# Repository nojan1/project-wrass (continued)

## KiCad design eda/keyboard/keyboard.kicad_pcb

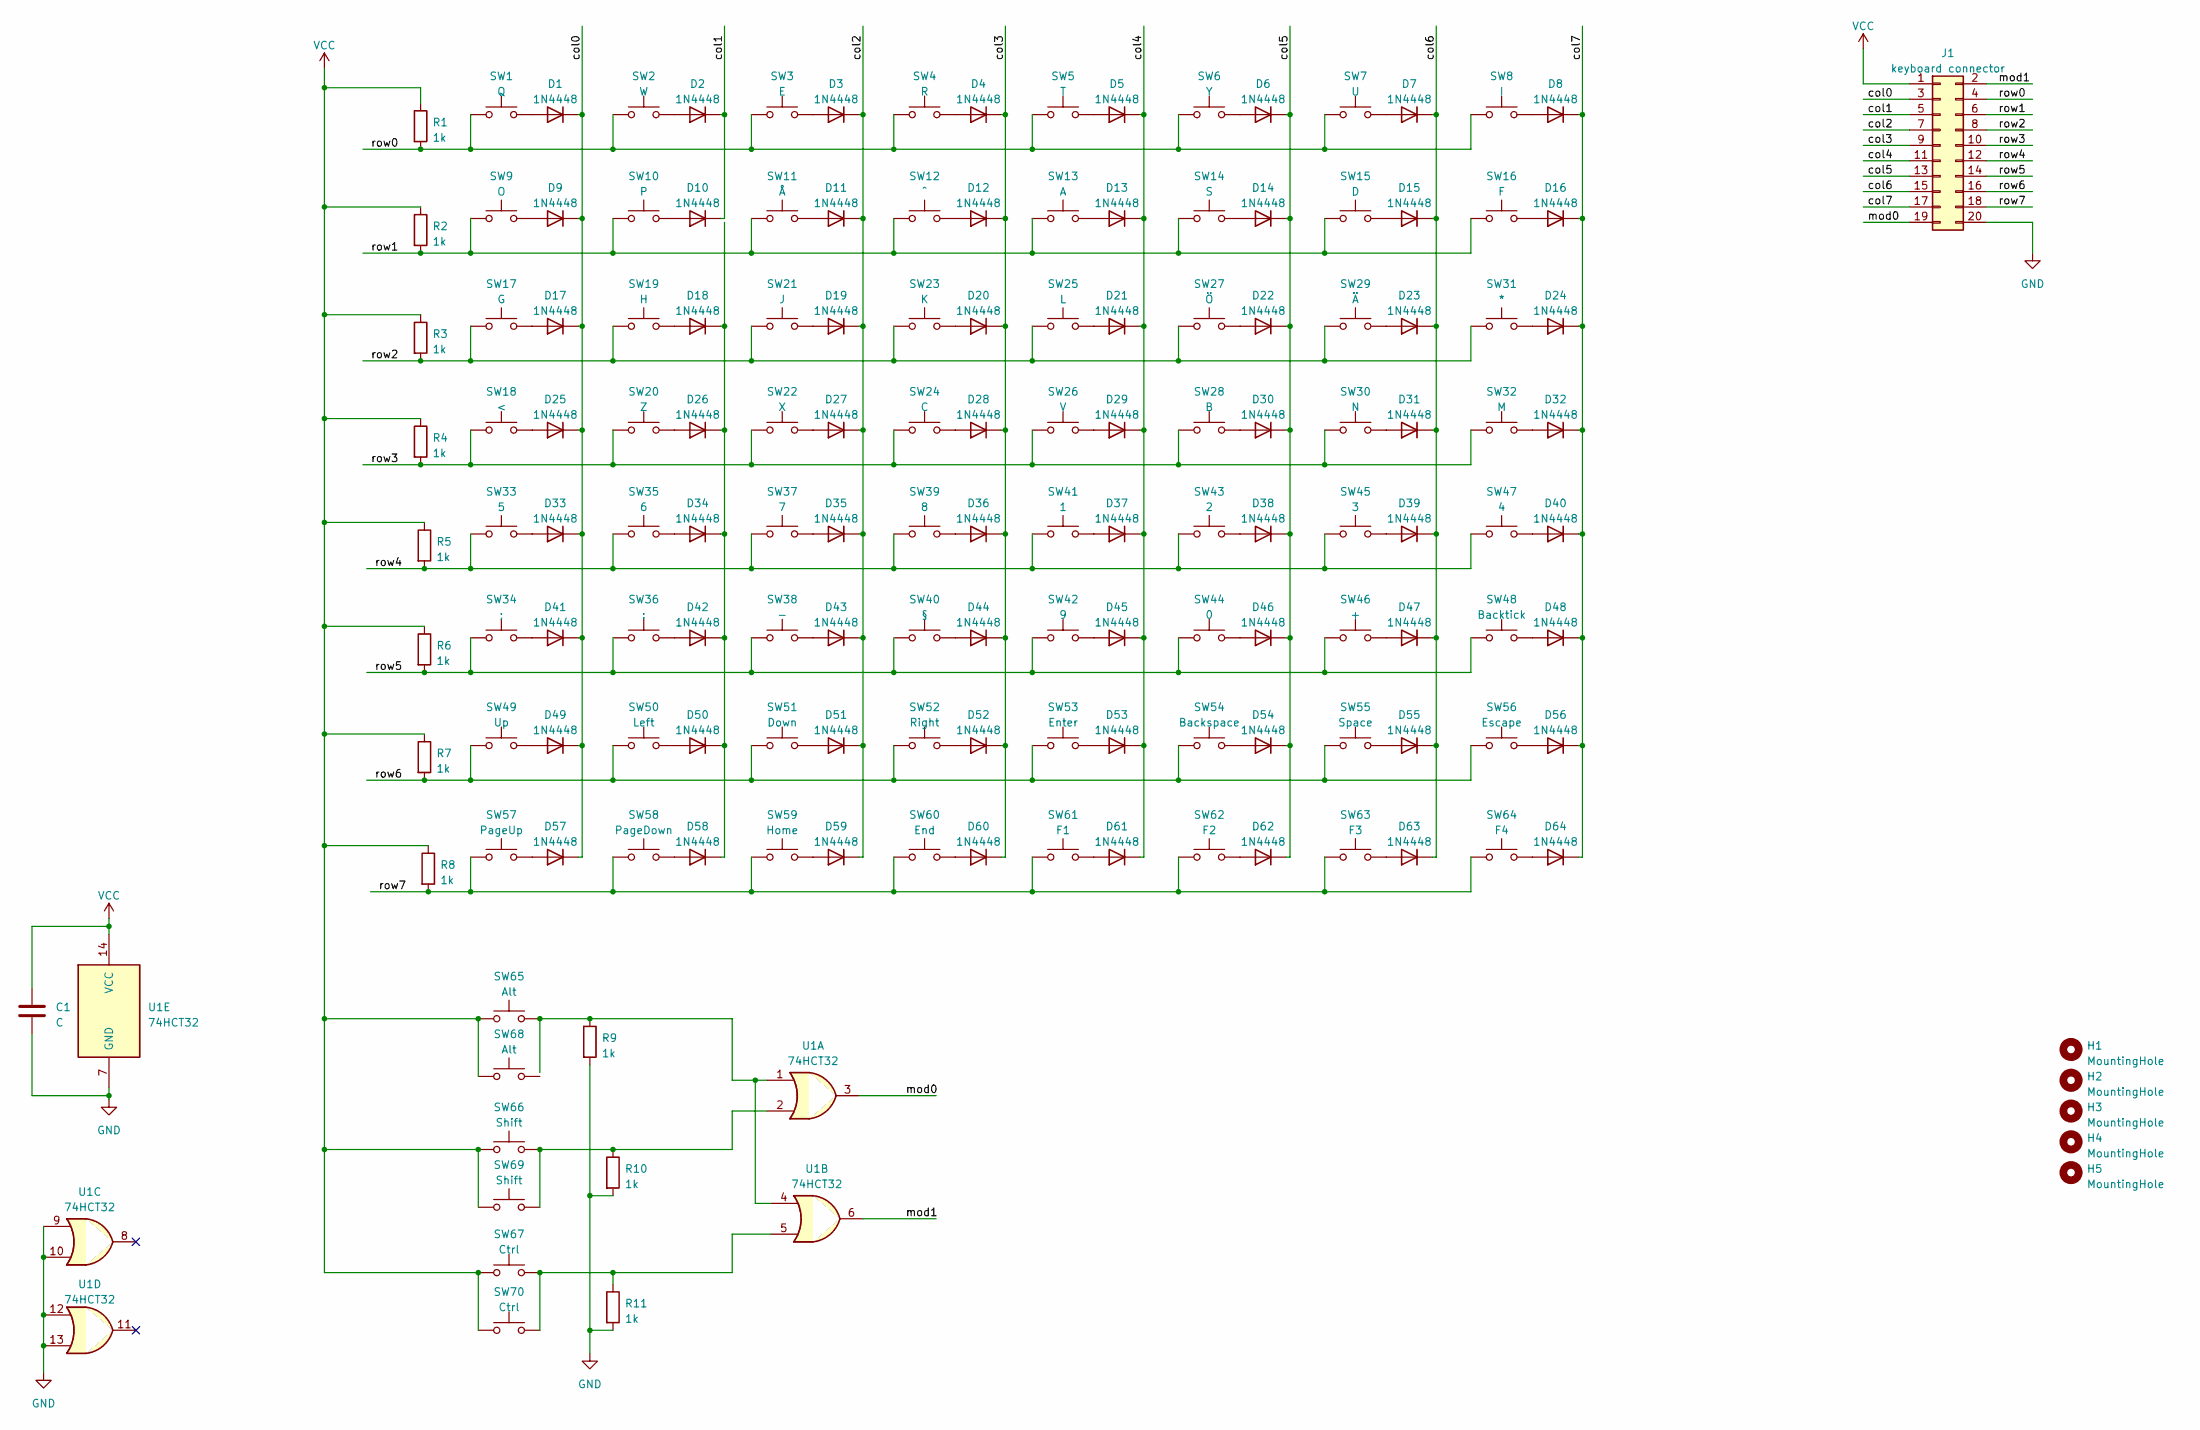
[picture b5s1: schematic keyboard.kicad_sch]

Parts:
C1: C
D1, D2, D3, D4, D5, D6, D7, D8, D9, D10, D11, D12, D13, D14, D15, D16, D17, D18, D19, D20, D21, D22, D23, D24, D25, D26, D27, D28, D29, D30, D31, D32, D33, D34, D35, D36, D37, D38, D39, D40, D41, D42, D43, D44, D45, D46, D47, D48, D49, D50, D51, D52, D53, D54, D55, D56, D57, D58, D59, D60, D61, D62, D63, D64: 1N4448; D_DO-35_SOD27_P7.62mm_Horizontal
H1, H2, H3, H4, H5: MountingHole; MountingHole_2.5mm
J1: keyboard connector; PinSocket_2x10_P2.54mm_Horizontal
R1, R2, R3, R4, R5, R6, R7, R8, R9, R10, R11: 1k
SW1: Q; SW_Cherry_MX_PCB_1.00u
SW2: W; SW_Cherry_MX_PCB_1.00u
SW3: E; SW_Cherry_MX_PCB_1.00u
SW4: R; SW_Cherry_MX_PCB_1.00u
SW5: T; SW_Cherry_MX_PCB_1.00u
SW6: Y; SW_Cherry_MX_PCB_1.00u
SW7: U; SW_Cherry_MX_PCB_1.00u
SW8: I; SW_Cherry_MX_PCB_1.00u
SW9: O; SW_Cherry_MX_PCB_1.00u
SW10: P; SW_Cherry_MX_PCB_1.00u
SW11: Å; SW_Cherry_MX_PCB_1.00u
SW12: ^; SW_Cherry_MX_PCB_1.00u
SW13: A; SW_Cherry_MX_PCB_1.00u
SW14: S; SW_Cherry_MX_PCB_1.00u
SW15: D; SW_Cherry_MX_PCB_1.00u
SW16: F; SW_Cherry_MX_PCB_1.00u
SW17: G; SW_Cherry_MX_PCB_1.00u
SW18: <; SW_Cherry_MX_PCB_1.00u
SW19: H; SW_Cherry_MX_PCB_1.00u
SW20: Z; SW_Cherry_MX_PCB_1.00u
SW21: J; SW_Cherry_MX_PCB_1.00u
SW22: X; SW_Cherry_MX_PCB_1.00u
SW23: K; SW_Cherry_MX_PCB_1.00u
SW24: C; SW_Cherry_MX_PCB_1.00u
SW25: L; SW_Cherry_MX_PCB_1.00u
SW26: V; SW_Cherry_MX_PCB_1.00u
SW27: Ö; SW_Cherry_MX_PCB_1.00u
SW28: B; SW_Cherry_MX_PCB_1.00u
SW29: Ä; SW_Cherry_MX_PCB_1.00u
SW30: N; SW_Cherry_MX_PCB_1.00u
SW31: *; SW_Cherry_MX_PCB_1.00u
SW32: M; SW_Cherry_MX_PCB_1.00u
SW33: 5; SW_Cherry_MX_PCB_1.00u
SW34: ;; SW_Cherry_MX_PCB_1.00u
SW35: 6; SW_Cherry_MX_PCB_1.00u
SW36: :; SW_Cherry_MX_PCB_1.00u
SW37: 7; SW_Cherry_MX_PCB_1.00u
SW38: -; SW_Cherry_MX_PCB_1.00u
SW39: 8; SW_Cherry_MX_PCB_1.00u
SW40: §; SW_Cherry_MX_PCB_1.00u
SW41: 1; SW_Cherry_MX_PCB_1.00u
SW42: 9; SW_Cherry_MX_PCB_1.00u
SW43: 2; SW_Cherry_MX_PCB_1.00u
SW44: 0; SW_Cherry_MX_PCB_1.00u
SW45: 3; SW_Cherry_MX_PCB_1.00u
SW46: +; SW_Cherry_MX_PCB_1.00u
SW47: 4; SW_Cherry_MX_PCB_1.00u
SW48: Backtick; SW_Cherry_MX_PCB_1.00u
SW49: Up; SW_Cherry_MX_PCB_1.00u
SW50: Left; SW_Cherry_MX_PCB_1.00u
SW51: Down; SW_Cherry_MX_PCB_1.00u
SW52: Right; SW_Cherry_MX_PCB_1.00u
SW53: Enter; SW_Cherry_MX_PCB_ISOEnter
SW54: Backspace; SW_Cherry_MX_PCB_2.00u
SW55: Space; SW_Cherry_MX_PCB_1.00u
SW56: Escape; SW_Cherry_MX_PCB_1.00u
SW57: PageUp; SW_Cherry_MX_PCB_1.00u
SW58: PageDown; SW_Cherry_MX_PCB_1.00u
SW59: Home; SW_Cherry_MX_PCB_1.00u
SW60: End; SW_Cherry_MX_PCB_1.00u
SW61: F1; SW_Cherry_MX_PCB_1.00u
SW62: F2; SW_Cherry_MX_PCB_1.00u
SW63: F3; SW_Cherry_MX_PCB_1.00u
SW64: F4; SW_Cherry_MX_PCB_1.00u
SW65, SW68: Alt; SW_Cherry_MX_PCB_1.25u
SW66: Shift; SW_Cherry_MX_PCB_1.25u
SW67, SW70: Ctrl; SW_Cherry_MX_PCB_1.25u
SW69: Shift; SW_Cherry_MX_PCB_2.75u
U1: 74HCT32; DIP-14_W10.16mm

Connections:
/col0: D1.1 (K), D9.1 (K), D17.1 (K), D25.1 (K), D33.1 (K), D41.1 (K), D49.1 (K), D57.1 (K), J1.3
/col1: D2.1 (K), D10.1 (K), J1.5
/col2: D3.1 (K), D11.1 (K), D19.1 (K), D27.1 (K), D35.1 (K), D43.1 (K), D51.1 (K), D59.1 (K), J1.7
/col3: D4.1 (K), D12.1 (K), D20.1 (K), D28.1 (K), D36.1 (K), D44.1 (K), D52.1 (K), D60.1 (K), J1.9
/col4: D5.1 (K), D13.1 (K), D21.1 (K), D29.1 (K), D37.1 (K), D45.1 (K), D53.1 (K), D61.1 (K), J1.11
/col5: D6.1 (K), D14.1 (K), D22.1 (K), D30.1 (K), D38.1 (K), D46.1 (K), D54.1 (K), D62.1 (K), J1.13
/col6: D7.1 (K), D15.1 (K), D23.1 (K), D31.1 (K), D39.1 (K), D47.1 (K), D55.1 (K), D63.1 (K), J1.15
/col7: D8.1 (K), D16.1 (K), D24.1 (K), D32.1 (K), D40.1 (K), D48.1 (K), D56.1 (K), D64.1 (K), J1.17
/mod0: J1.19, U1.3
/mod1: J1.2, U1.6
/row0: J1.4, R1.2, SW1.1, SW2.1, SW3.1, SW4.1, SW5.1, SW6.1, SW7.1, SW8.1
/row1: J1.6, R2.2, SW9.1, SW10.1, SW11.1, SW12.1, SW13.1, SW14.1, SW15.1, SW16.1
/row2: J1.8, R3.2, SW17.1, SW19.1, SW21.1, SW23.1, SW25.1, SW27.1, SW29.1, SW31.1
/row3: J1.10, R4.2, SW18.1, SW20.1, SW22.1, SW24.1, SW26.1, SW28.1, SW30.1, SW32.1
/row4: J1.12, R5.2, SW33.1, SW35.1, SW37.1, SW39.1, SW41.1, SW43.1, SW45.1, SW47.1
/row5: J1.14, R6.2, SW34.1, SW36.1, SW38.1, SW40.1, SW42.1, SW44.1, SW46.1, SW48.1
/row6: J1.16, R7.2, SW49.1, SW50.1, SW51.1, SW52.1, SW53.1, SW54.1, SW55.1, SW56.1
/row7: J1.18, R8.2, SW57.1, SW58.1, SW59.1, SW60.1, SW61.1, SW62.1, SW63.1, SW64.1
GND: C1.2, J1.20, R9.2, R10.2, R11.2, U1.7 (GND), U1.9, U1.10, U1.12, U1.13
unnamed: D1.2 (A), SW1.2
unnamed: D2.2 (A), SW2.2
unnamed: D3.2 (A), SW3.2
unnamed: D4.2 (A), SW4.2
unnamed: D5.2 (A), SW5.2
unnamed: D6.2 (A), SW6.2
unnamed: D7.2 (A), SW7.2
unnamed: D8.2 (A), SW8.2
unnamed: D9.2 (A), SW9.2
unnamed: D10.2 (A), SW10.2
unnamed: D11.2 (A), SW11.2
unnamed: D12.2 (A), SW12.2
unnamed: D13.2 (A), SW13.2
unnamed: D14.2 (A), SW14.2
unnamed: D15.2 (A), SW15.2
unnamed: D16.2 (A), SW16.2
unnamed: D17.2 (A), SW17.2
unnamed: D18.2 (A), SW19.2
unnamed: D18.1 (K), D26.1 (K), D34.1 (K), D42.1 (K), D50.1 (K), D58.1 (K)
unnamed: D19.2 (A), SW21.2
unnamed: D20.2 (A), SW23.2
unnamed: D21.2 (A), SW25.2
unnamed: D22.2 (A), SW27.2
unnamed: D23.2 (A), SW29.2
unnamed: D24.2 (A), SW31.2
unnamed: D25.2 (A), SW18.2
unnamed: D26.2 (A), SW20.2
unnamed: D27.2 (A), SW22.2
unnamed: D28.2 (A), SW24.2
unnamed: D29.2 (A), SW26.2
unnamed: D30.2 (A), SW28.2
unnamed: D31.2 (A), SW30.2
unnamed: D32.2 (A), SW32.2
unnamed: D33.2 (A), SW33.2
unnamed: D34.2 (A), SW35.2
unnamed: D35.2 (A), SW37.2
unnamed: D36.2 (A), SW39.2
unnamed: D37.2 (A), SW41.2
unnamed: D38.2 (A), SW43.2
unnamed: D39.2 (A), SW45.2
unnamed: D40.2 (A), SW47.2
unnamed: D41.2 (A), SW34.2
unnamed: D42.2 (A), SW36.2
unnamed: D43.2 (A), SW38.2
unnamed: D44.2 (A), SW40.2
unnamed: D45.2 (A), SW42.2
unnamed: D46.2 (A), SW44.2
unnamed: D47.2 (A), SW46.2
unnamed: D48.2 (A), SW48.2
unnamed: D49.2 (A), SW49.2
unnamed: D50.2 (A), SW50.2
unnamed: D51.2 (A), SW51.2
unnamed: D52.2 (A), SW52.2
unnamed: D53.2 (A), SW53.2
unnamed: D54.2 (A), SW54.2
unnamed: D55.2 (A), SW55.2
unnamed: D56.2 (A), SW56.2
unnamed: D57.2 (A), SW57.2
unnamed: D58.2 (A), SW58.2
unnamed: D59.2 (A), SW59.2
unnamed: D60.2 (A), SW60.2
unnamed: D61.2 (A), SW61.2
unnamed: D62.2 (A), SW62.2
unnamed: D63.2 (A), SW63.2
unnamed: D64.2 (A), SW64.2
unnamed: R9.1, SW65.2, U1.1, U1.4
unnamed: R10.1, SW66.2, SW69.2, U1.2
unnamed: R11.1, SW67.2, SW70.2, U1.5
VCC: C1.1, J1.1, R1.1, R2.1, R3.1, R4.1, R5.1, R6.1, R7.1, R8.1, SW65.1, SW66.1, SW67.1, SW68.1, SW69.1, SW70.1, U1.14 (VCC)

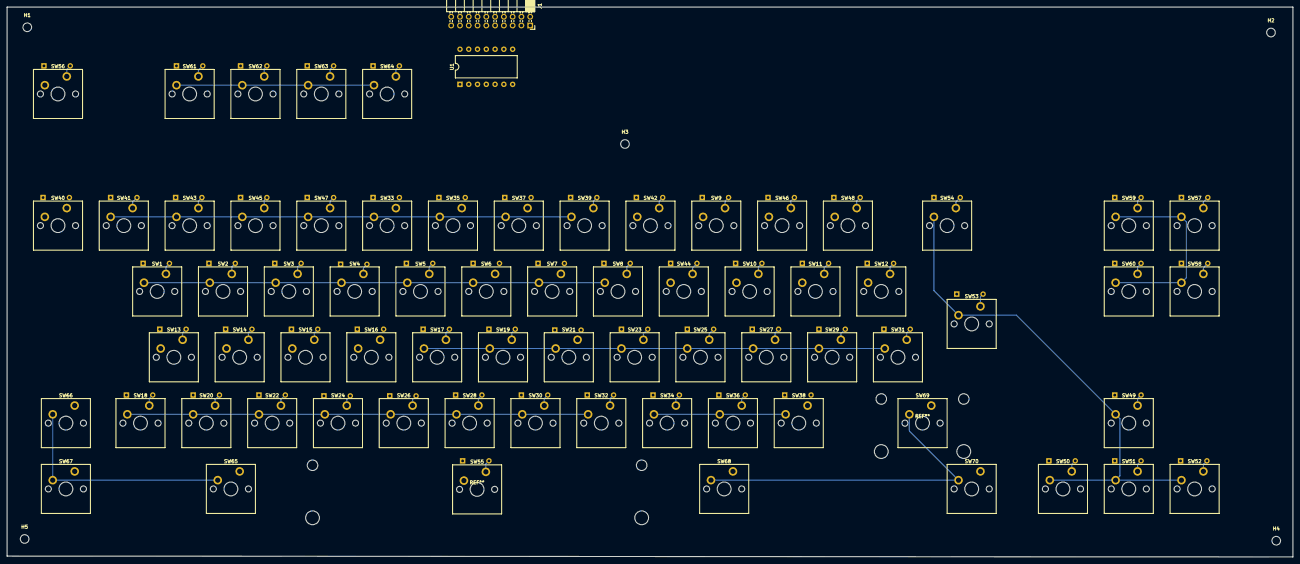
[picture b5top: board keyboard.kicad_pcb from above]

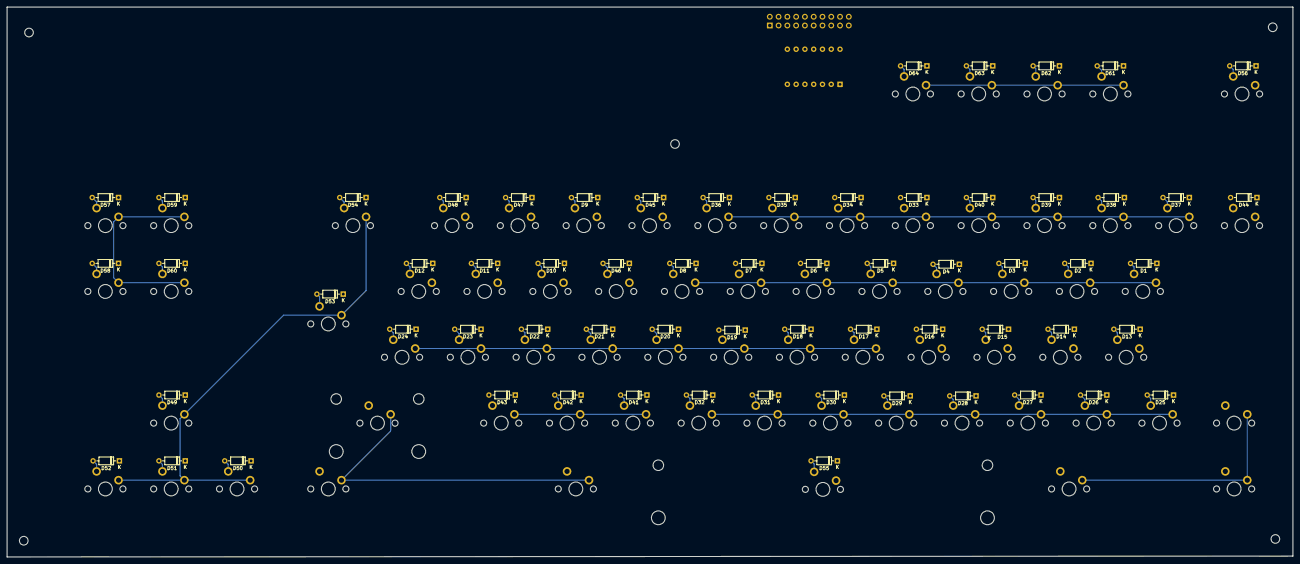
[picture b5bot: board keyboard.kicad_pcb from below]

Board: 2 copper layers, 372.1 x 159.1 mm, 141 parts (64 on the bottom side), 88 nets.

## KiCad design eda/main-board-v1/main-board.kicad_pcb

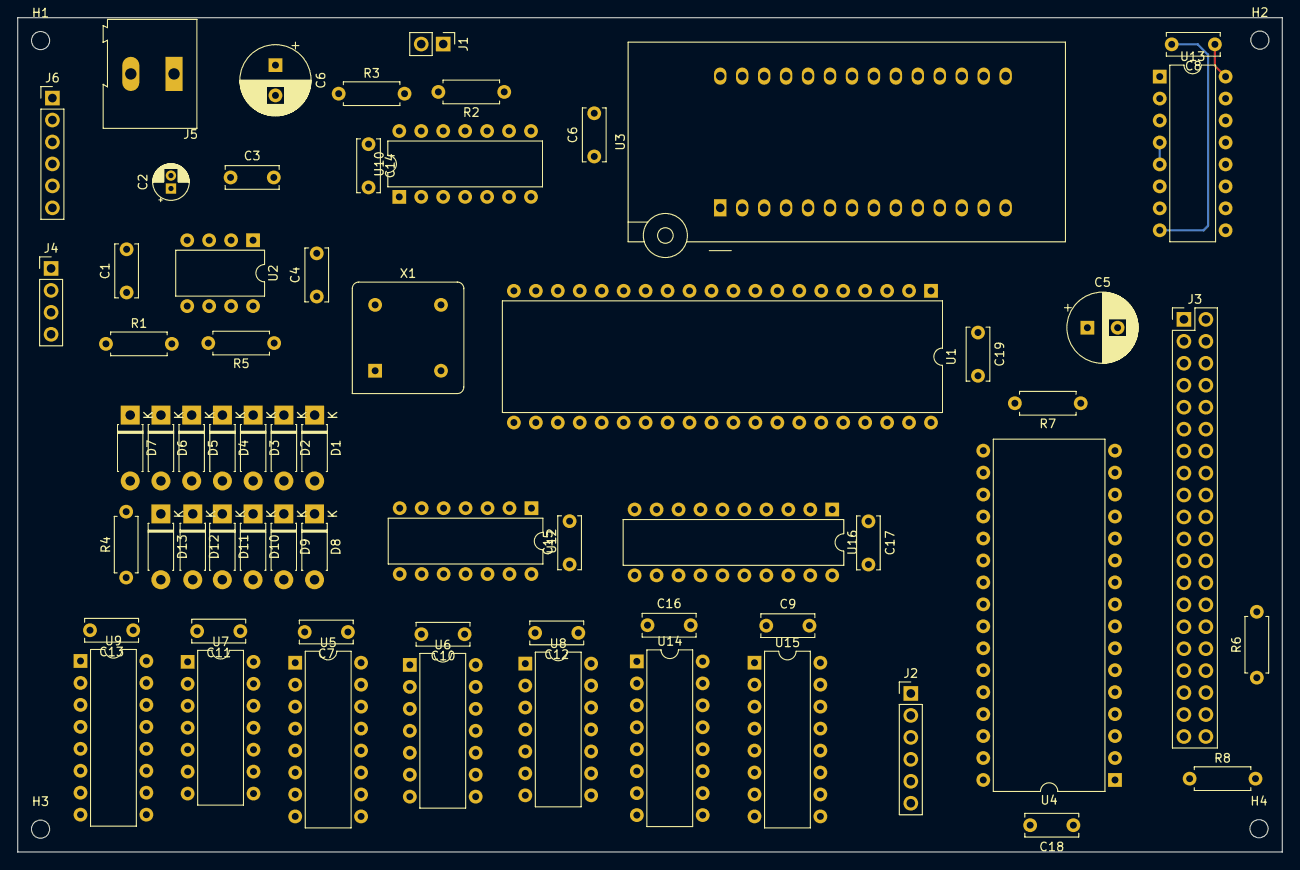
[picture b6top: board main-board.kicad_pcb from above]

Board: 2 copper layers, 146.3 x 96.5 mm, 67 parts (0 on the bottom side), 97 nets.

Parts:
C1: 10n; C_Disc_D6.0mm_W2.5mm_P5.00mm
C2: 10u; CP_Radial_D4.0mm_P1.50mm
C3, C4, C6, C7, C8, C9, C10, C11, C12, C13, C14, C15, C16, C17, C18, C19: 100n; C_Disc_D6.0mm_W2.5mm_P5.00mm
C5: 1u; CP_Radial_D8.0mm_P3.50mm
C6#2: 3u; CP_Radial_D8.0mm_P3.50mm
D1, D2, D3, D4, D5, D6, D7, D8, D9, D10, D11, D12, D13: 1N4007; D_DO-41_SOD81_P7.62mm_Horizontal
H1, H2, H3, H4: MountingHole; MountingHole_2.1mm
J1: RomHighSel; PinHeader_1x02_P2.54mm_Vertical
J2: Membank block; PinHeader_1x06_P2.54mm_Vertical
J3: Expansion; PinHeader_2x20_P2.54mm_Vertical
J4: $1-3 latch; PinHeader_1x04_P2.54mm_Vertical
J5: PWR; TerminalBlock_Altech_AK300-2_P5.00mm
J6: CS_leds; PinHeader_1x06_P2.54mm_Vertical
R1: 47k; R_Axial_DIN0207_L6.3mm_D2.5mm_P7.62mm_Horizontal
R2: 1M; R_Axial_DIN0207_L6.3mm_D2.5mm_P7.62mm_Horizontal
R3, R4, R6, R7, R8: 10k; R_Axial_DIN0207_L6.3mm_D2.5mm_P7.62mm_Horizontal
R5: 1k; R_Axial_DIN0207_L6.3mm_D2.5mm_P7.62mm_Horizontal
U1: W65C02SxP; DIP-40_W15.24mm
U2: NA555P; DIP-8_W7.62mm
U3: 28C256; DIP_Socket-28_W11.9_W12.7_W15.24_W17.78_W18.5_3M_228-1277-0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
U4: AS6C4008-55PCN; DIP-32_W15.24mm
U5, U13: 74HCT138; DIP-16_W7.62mm
U6, U12: 74HCT32; DIP-14_W7.62mm
U7: 74HCT08; DIP-14_W7.62mm
U8: 74HCT30; DIP-14_W7.62mm
U9: 74HCT139; DIP-16_W7.62mm
U10: 74HCT00; DIP-14_W7.62mm
U14, U15: 74LHCT157; DIP-16_W7.62mm
U16: 74HCT273; DIP-20_W7.62mm
X1: 4Mhz; Oscillator_DIP-8

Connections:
/A0: J3.3, U1.9 (A0)
/A1: J3.5, U1.10 (A1)
/A2: J3.7, U1.11 (A2)
/A3: J3.9, U1.12 (A3)
/A4: J3.11, U1.13 (A4)
/A5: J3.13, U1.14 (A5)
/A6: J3.15, U1.15 (A6)
/A7: J3.17, U1.16 (A7)
/A8: J3.19, U1.17 (A8)
/A9: J3.21, U1.18 (A9)
/A10: J3.23, U1.19 (A10)
/A11: J3.25, U1.20 (A11)
/A12: J3.27, U1.22 (A12)
/A13: J3.29, U1.23 (A13)
/A14: J3.31, U1.24 (A14)
/A15: J3.33, U1.25 (A15)
/Address decode/A0: U3.10 (A0), U4.12 (A0), U9.13 (A1)
/Address decode/A1: U3.9 (A1), U4.11 (A1), U9.14 (A0)
/Address decode/A2: D11.2 (A), U3.8 (A2), U4.10 (A2)
/Address decode/A3: D10.2 (A), U3.7 (A3), U4.9 (A3)
/Address decode/A4: D9.2 (A), U3.6 (A4), U4.8 (A4)
/Address decode/A5: D8.2 (A), U3.5 (A5), U4.7 (A5)
/Address decode/A6: D7.2 (A), U3.4 (A6), U4.6 (A6), U13.1 (A0)
/Address decode/A7: D6.2 (A), U3.3 (A7), U4.5 (A7), U13.2 (A1)
/Address decode/A8: D5.2 (A), U3.25 (A8), U4.27 (A8), U13.3 (A2)
/Address decode/A9: D4.2 (A), U3.24 (A9), U4.26 (A9), U9.3 (A1)
/Address decode/A10: D3.2 (A), U3.21 (A10), U4.23 (A10), U9.2 (A0)
/Address decode/A11: D2.2 (A), U3.23 (A11), U4.25 (A11), U10.1
/Address decode/A12: D1.2 (A), U3.2 (A12), U4.4 (A12), U10.2
/Address decode/A13: U3.26 (A13), U5.1 (A0), U14.3 (I1a)
/Address decode/A14: U5.2 (A1), U14.6 (I1b)
/Address decode/A15: U5.3 (A2), U14.10 (I1c)
/Address decode/Addr0Latch: U9.12 (O0), U16.11 (Cp)
/Address decode/Addr1Latch: J4.2, U9.11 (O1)
/Address decode/Addr2Latch: J4.3, U9.10 (O2)
/Address decode/Addr3Latch: J4.4, U9.9 (O3)
/Address decode/R~W: J3.37, U1.34 (R/~W), U4.29 (WE#), U10.9, U10.10
/Address decode/~Io1Cs: J6.5, U8.3, U9.5 (O1), U13.4 (E1), U13.5 (E2)
/Address decode/~Io2Cs: J6.6, U6.8, U8.4
/Address decode/~RamCs: J6.2, U4.22 (CE#), U12.3
/Address decode/~RamOe: U4.24 (OE#), U8.8, U12.1
/Address decode/~RomCs: U3.20 (~CS), U7.3
/Address decode/~RomOe: U3.22 (~OE), U10.8
/D0: J3.4, U1.33 (D0), U3.11 (D0), U4.13 (DQ0), U16.3 (D0)
/D1: J3.6, U1.32 (D1), U3.12 (D1), U4.14 (DQ1), U16.4 (D1)
/D2: J3.8, U1.31 (D2), U3.13 (D2), U4.15 (DQ2), U16.7 (D2)
/D3: J3.10, U1.30 (D3), U3.15 (D3), U4.17 (DQ3), U16.8 (D3)
/D4: J3.12, U1.29 (D4), U3.16 (D4), U4.18 (DQ4), U16.13 (D4)
/D5: J3.14, U1.28 (D5), U3.17 (D5), U4.19 (DQ5), U16.14 (D5)
/D6: J3.16, U1.27 (D6), U3.18 (D6), U4.20 (DQ6), U16.17 (D6)
/D7: J3.18, U1.26 (D7), U3.19 (D7), U4.21 (DQ7), U16.18 (D7)
/IO Address Decode/IoSelect0: J3.20, U13.15 (O0)
/IO Address Decode/IoSelect1: J3.22, U13.14 (O1)
/IO Address Decode/IoSelect2: J3.24, U13.13 (O2)
/IO Address Decode/IoSelect3: J3.26, U13.12 (O3)
/IO Address Decode/IoSelect4: J3.28, U13.11 (O4)
/IO Address Decode/IoSelect5: J3.30, U13.10 (O5)
/IO Address Decode/IoSelect6: J3.32, U13.9 (O6)
/IO Address Decode/IoSelect7: J3.34, U13.7 (O7)
/Memory banking/AB13: U4.28 (A13), U14.4 (Za)
/Memory banking/AB14: U4.3 (A14), U14.7 (Zb)
/Memory banking/AB15: U4.31 (A15), U14.9 (Zc)
/Memory banking/AB16: U4.2 (A16), U14.12 (Zd)
/Memory banking/AB17: U4.30 (A17), U15.4 (Za)
/Memory banking/AB18: U4.1 (A18), U15.7 (Zb)
/Memory banking/~Reset: J3.36, R5.2, U1.40 (~RES), U10.11, U16.1 (~Mr)
Clock: J3.35, U1.37 (ϕ0), X1.5 (OUT)
GND: C1.2, C2.2, C3.2, C4.2, C5.2, C6.2, C6#2.2, C7.2, C8.2, C9.2, C10.2, C11.2, C12.2, C13.2, C14.2, C15.2, C16.2, C17.2, C18.2, C19.2, J2.1, J3.2, J4.1, J5.2, R3.2, R4.2, U1.21 (VSS), U2.1 (GND), U3.14 (GND), U4.16 (VSS), U5.4 (E1), U5.5 (E2), U5.8 (GND), U6.7 (GND), U7.4, U7.5, U7.7 (GND), U7.9, U7.10, U7.12, U7.13, U8.7 (GND), U9.8 (GND), U10.4, U10.5, U10.7 (GND), U13.8 (GND), U14.8 (GND), U14.13 (I1d), U14.15 (E), U15.3 (I1a), U15.6 (I1b), U15.8 (GND), U15.10 (I1c), U15.11 (I0c), U15.13 (I1d), U15.14 (I0d), U15.15 (E), U16.10 (GND), X1.4 (GND)
unnamed: D1.1 (K), D2.1 (K), D3.1 (K), D4.1 (K), D5.1 (K), D6.1 (K), D7.1 (K), D8.1 (K), D9.1 (K), D10.1 (K), D11.1 (K), D12.1 (K), D13.1 (K), R4.1, U9.15 (E)
unnamed: J1.2, R3.1, U3.1 (A14)
unnamed: J2.2, U14.2 (I0a), U16.9 (Q3)
unnamed: J2.3, U14.5 (I0b), U16.12 (Q4)
unnamed: J2.4, U14.11 (I0c), U16.15 (Q5)
unnamed: J2.5, U15.2 (I0a), U16.16 (Q6)
unnamed: J2.6, U15.5 (I0b), U16.19 (Q7)
unnamed: J3.38, R7.2, U1.6 (~NMI)
unnamed: J3.39, R8.2, U1.2 (RDY), U1.36 (BE)
unnamed: J3.40, R6.2, U1.4 (~IRQ)
unnamed: J6.3, U6.3, U7.1, U8.1
unnamed: J6.4, U6.6, U7.2, U8.2
unnamed: C1.1, U2.5 (CV)
unnamed: C2.1, R1.2, U2.6 (THR), U2.7 (DIS)
unnamed: C3.1, R2.2, U2.2 (TR)
unnamed: U5.9 (O6), U6.1
unnamed: U5.7 (O7), U6.4
unnamed: U6.11, U9.1 (E)
unnamed: U6.9, U9.7 (O3)
unnamed: U6.12, U10.3
RamBank4Enable: U6.10, U16.2 (Q0)
RamBank5Enable: U6.2, U16.5 (Q1)
RamBank6Enable: U6.5, U16.6 (Q2)
Reset: U2.3 (Q), U10.12, U10.13
VCC: C4.1, C5.1, C6.1, C6#2.1, C7.1, C8.1, C9.1, C10.1, C11.1, C12.1, C13.1, C14.1, C15.1, C16.1, C17.1, C18.1, C19.1, J1.1, J3.1, J5.1, J6.1, R1.1, R2.1, R5.1, R6.1, R7.1, R8.1, U1.8 (VDD), U2.4 (R), U2.8 (VCC), U3.27 (~WE), U3.28 (VCC), U4.32 (VCC), U5.6 (E3), U5.16 (VCC), U6.14 (VCC), U7.14 (VCC), U8.5, U8.6, U8.11, U8.12, U8.14 (VCC), U9.16 (VCC), U10.14 (VCC), U13.6 (E3), U13.16 (VCC), U14.14 (I0d), U14.16 (VCC), U15.16 (VCC), U16.20 (VCC), X1.8 (Vcc)
~8000: U5.11 (O4), U14.1 (S), U15.1 (S)
~A000: U5.10 (O5), U6.13
~Clock: D13.2 (A), U1.3 (ϕ1), U12.2
~LowestBlock: D12.2 (A), U5.15 (O0)

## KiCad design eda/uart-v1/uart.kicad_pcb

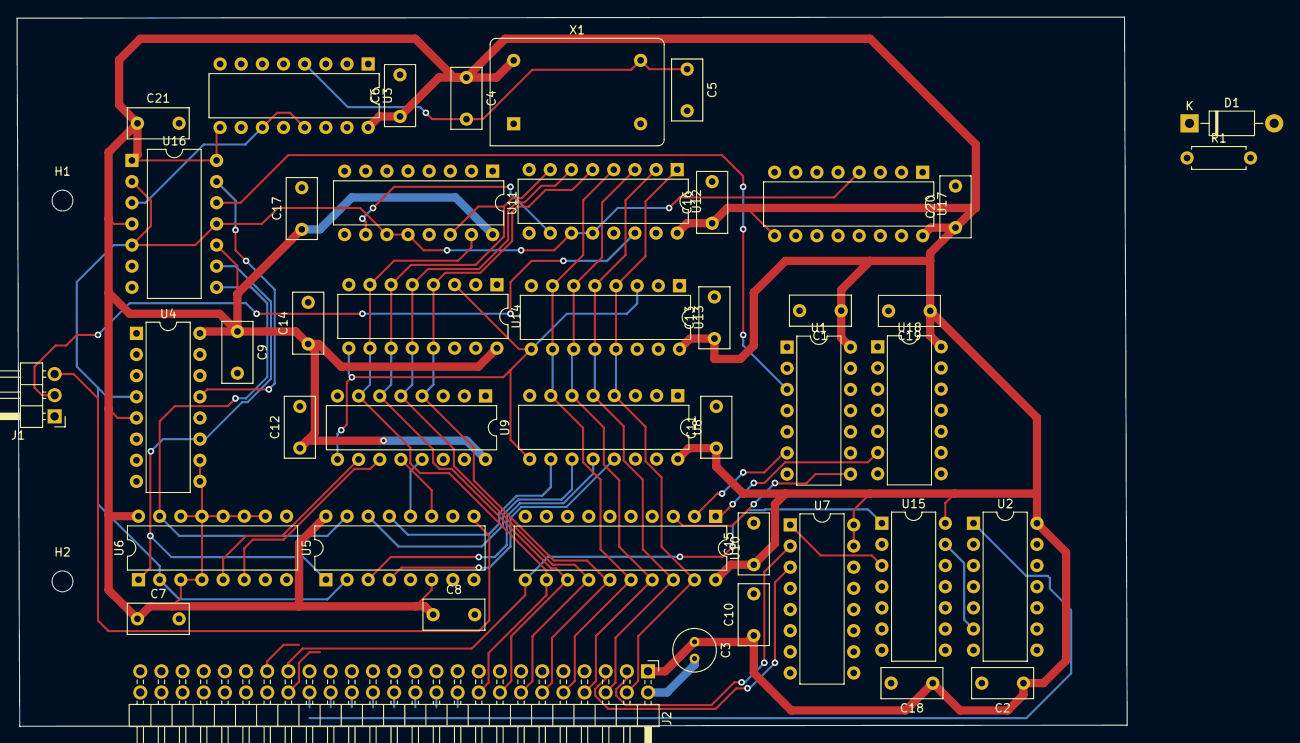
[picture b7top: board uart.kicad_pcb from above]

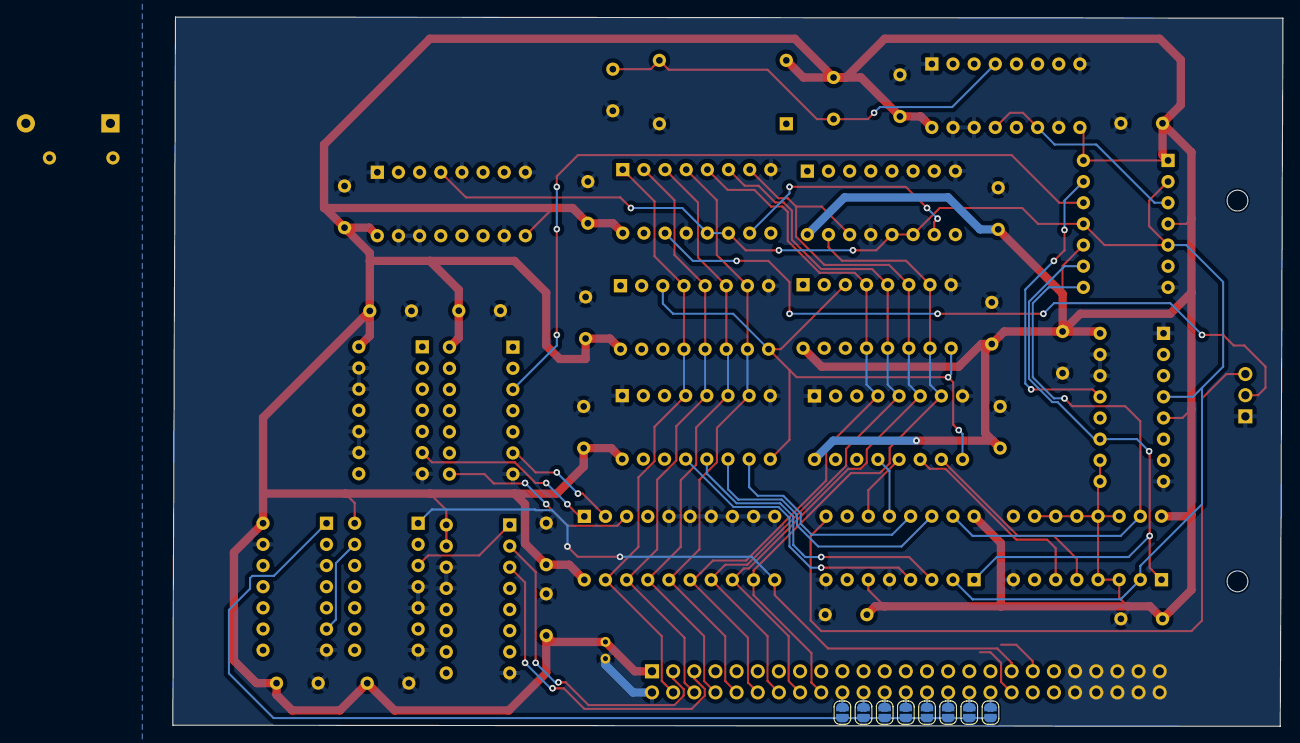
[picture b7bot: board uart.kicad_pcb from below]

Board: 2 copper layers, 133.3 x 85.2 mm, 54 parts (8 on the bottom side), 69 nets.

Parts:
C1, C2, C6, C7, C8, C9, C10, C11, C12, C13, C14, C15, C16, C17, C18, C19, C20, C21: 0.1uf; C_Rect_L7.2mm_W3.5mm_P5.00mm_FKS2_FKP2_MKS2_MKP2
C3: 100nf; C_Radial_D5.0mm_H7.0mm_P2.00mm
C4, C5: 22pf; C_Rect_L7.2mm_W3.5mm_P5.00mm_FKS2_FKP2_MKS2_MKP2
D1: 1N4001; D_DO-41_SOD81_P10.16mm_Horizontal
H1, H2: MountingHole; MountingHole_2.5mm
J1: UART; PinHeader_1x03_P2.54mm_Horizontal
J2: Conn_02x25_Odd_Even; PinHeader_2x25_P2.54mm_Horizontal
JP1, JP2, JP3, JP4, JP5, JP6, JP7, JP8: SolderJumper_2_Open; SolderJumper-2_P1.3mm_Open_RoundedPad1.0x1.5mm
R1: 10K; R_Axial_DIN0207_L6.3mm_D2.5mm_P7.62mm_Horizontal
U1: 74HCT08; DIP-14_W7.62mm
U2: 74HCT14; DIP-14_W7.62mm
U3, U4, U17: 74HCT193; DIP-16_W7.62mm
U5, U6: 74HCT165; DIP-16_W7.62mm
U7: 74HCT139; DIP-16_W7.62mm
U8, U9, U13, U14: CD74HCT40105E; DIP-16_W7.62mm
U10: 74HCT574; DIP-20_W7.62mm
U11, U12: 74HCT595; DIP-16_W7.62mm
U15: 74HCT00; DIP-14_W7.62mm
U16: 74HCT74; DIP-14_W10.16mm
U18: 74HCT32; DIP-14_W7.62mm
X1: 1.8xx; Oscillator_DIP-14

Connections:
/Expansion header/A0: J2.5, U7.2 (A0)
/Expansion header/A1: J2.7, U7.3 (A1)
/Expansion header/Clock: J2.39, U10.11 (Cp), U15.1
/Expansion header/D0: J2.4, U8.4 (D0), U10.19 (Q0), U12.1 (QB), U13.13 (Q0)
/Expansion header/D1: J2.6, U8.5 (D1), U10.18 (Q1), U12.2 (QC), U13.12 (Q1)
/Expansion header/D2: J2.8, U8.6 (D2), U10.17 (Q2), U12.3 (QD), U13.11 (Q2)
/Expansion header/D3: J2.10, U8.7 (D3), U10.16 (Q3), U12.4 (QE), U13.10 (Q3)
/Expansion header/D4: J2.12, U9.4 (D0), U10.15 (Q4), U12.5 (QF), U14.13 (Q0)
/Expansion header/D5: J2.14, U9.5 (D1), U10.14 (Q5), U12.6 (QG), U14.12 (Q1)
/Expansion header/D6: J2.16, U9.6 (D2), U10.13 (Q6), U11.14 (SER), U12.7 (QH), U14.11 (Q2)
/Expansion header/D7: J2.18, U9.7 (D3), U10.12 (Q7), U11.15 (QA), U14.10 (Q3)
/Expansion header/R~W: J2.41, U2.9
/Expansion header/~CS: JP1.2 (B), JP2.2 (B), JP3.2 (B), JP4.2 (B), JP5.2 (B), JP6.2 (B), JP7.2 (B), JP8.2 (B), U2.1
/Expansion header/~RST: J2.40, U2.5
/address_decode/TransmitEnable: U2.10, U8.3 (SI), U9.3 (SI)
/address_decode/~RecieveEnable: U13.1 (~THREE-STATE_CONTROL), U14.1 (~THREE-STATE_CONTROL), U18.3
/address_decode/~StatusEnable: U10.1 (OE), U18.6
/clock/UartClock: U4.4 (DOWN), U5.2 (CP), U6.2 (CP), U11.11 (SRCLK), U11.12 (RCLK), U12.11 (SRCLK), U12.12 (RCLK), U16.3 (C), U16.9 (Q), U17.4 (DOWN)
/recieve/DataAvailable: U1.11, U10.4 (D2)
/recieve/FIFO Recieve/SI: U2.4, U13.3 (SI), U14.3 (SI)
/recieve/FIFO Recieve/SO: U13.15 (~SO), U14.15 (~SO)
/recieve/RX: J1.2, U12.14 (SER), U15.9
/recieve/RecieveBufferFull: U1.8, U10.3 (D1)
/recieve/Reset: U2.6, U8.9 (MR), U9.9 (MR), U13.9 (MR), U14.9 (MR)
/transmit/FIFO Transmit/DOR: U1.3, U16.2 (D)
/transmit/FIFO Transmit/Q0: U5.4 (D5), U8.13 (Q0)
/transmit/FIFO Transmit/Q1: U5.3 (D4), U8.12 (Q1)
/transmit/FIFO Transmit/Q2: U5.14 (D3), U8.11 (Q2)
/transmit/FIFO Transmit/Q3: U5.13 (D2), U8.10 (Q3)
/transmit/FIFO Transmit/Q4: U5.12 (D1), U9.13 (Q0)
/transmit/FIFO Transmit/Q5: U5.11 (D0), U9.12 (Q1)
/transmit/FIFO Transmit/Q6: U6.6 (D7), U9.11 (Q2)
/transmit/FIFO Transmit/Q7: U6.5 (D6), U9.10 (Q3)
/transmit/InputBufferFull: U1.6, U10.2 (D0)
/transmit/TX: J1.3, U5.9 (Q7)
/transmit/~ClockEnable: U5.15 (~CE), U6.15 (~CE), U8.15 (~SO), U9.15 (~SO), U16.6 (~Q)
/transmit/~LatchShiftRegisters: U4.11 (~LOAD), U5.1 (~PL), U6.1 (~PL), U16.5 (Q)
GND: C1.2, C2.2, C3.2, C5.2, C6.2, C7.2, C8.2, C9.2, C10.2, C11.2, C12.2, C13.2, C14.2, C15.2, C16.2, C17.2, C18.2, C19.2, C20.2, C21.2, J1.1, J2.2, J2.3, J2.20, J2.37, J2.38, J2.45, J2.46, U1.7 (GND), U2.7 (GND), U2.13, U3.1 (B), U3.8 (GND), U3.10 (C), U3.14 (CLR), U3.15 (A), U4.1 (B), U4.8 (GND), U4.14 (CLR), U4.15 (A), U5.5 (D6), U5.8 (GND), U6.8 (GND), U7.8 (GND), U7.13 (A1), U7.14 (A0), U8.1 (~THREE-STATE_CONTROL), U8.8 (GND), U9.1 (~THREE-STATE_CONTROL), U9.8 (GND), U10.5 (D3), U10.6 (D4), U10.7 (D5), U10.8 (D6), U10.9 (D7), U10.10 (GND), U11.8 (GND), U11.13 (~OE), U12.8 (GND), U12.13 (~OE), U13.8 (GND), U14.8 (GND), U15.4, U15.5, U15.7 (GND), U16.7 (GND), U17.1 (B), U17.5 (UP), U17.8 (GND), U17.10 (C), U17.14 (CLR), U17.15 (A), U18.7 (GND), U18.9, U18.10, U18.12, U18.13, X1.7 (GND)
unnamed: D1.2 (A), R1.2, U2.3, U15.13, U17.13 (~BO)
unnamed: J2.22, JP1.1 (A)
unnamed: J2.24, JP2.1 (A)
unnamed: J2.26, JP3.1 (A)
unnamed: J2.28, JP4.1 (A)
unnamed: J2.30, JP5.1 (A)
unnamed: J2.32, JP6.1 (A)
unnamed: J2.34, JP7.1 (A)
unnamed: J2.36, JP8.1 (A)
unnamed: C4.2, C5.1, U3.4 (DOWN), X1.8 (OUT)
unnamed: U5.10 (DS), U6.9 (Q7)
unnamed: U7.1 (E), U15.3
unnamed: U2.11, U7.4 (O0)
unnamed: U7.5 (O1), U18.1
unnamed: U7.6 (O2), U18.4
unnamed: U1.5, U8.2 (DIR)
unnamed: U1.1, U8.14 (DOR)
unnamed: U1.4, U9.2 (DIR)
unnamed: U1.2, U9.14 (DOR)
unnamed: U11.10 (~SRCLR), U12.10 (~SRCLR), U15.8, U15.12, U17.11 (~LOAD)
unnamed: U1.10, U13.2 (DIR)
unnamed: U1.12, U13.14 (DOR)
unnamed: U1.9, U14.2 (DIR)
unnamed: U1.13, U14.14 (DOR)
unnamed: U2.2, U15.2
unnamed: U15.10, U15.11
unnamed: U4.13 (~BO), U16.1 (~R)
unnamed: U3.11 (~LOAD), U3.13 (~BO), U16.11 (C)
unnamed: U16.8 (~Q), U16.12 (D)
unnamed: U2.8, U18.2, U18.5
VCC: C1.1, C2.1, C3.1, C4.1, C6.1, C7.1, C8.1, C9.1, C10.1, C11.1, C12.1, C13.1, C14.1, C15.1, C16.1, C17.1, C18.1, C19.1, C20.1, C21.1, J2.1, R1.1, U1.14 (VCC), U2.14 (VCC), U3.9 (D), U3.16 (VCC), U4.5 (UP), U4.9 (D), U4.10 (C), U4.16 (VCC), U5.6 (D7), U5.16 (VCC), U6.3 (D4), U6.4 (D5), U6.10 (DS), U6.11 (D0), U6.12 (D1), U6.13 (D2), U6.14 (D3), U6.16 (VCC), U7.15 (E), U7.16 (VCC), U8.16 (VCC), U9.16 (VCC), U10.20 (VCC), U11.16 (VCC), U12.16 (VCC), U13.16 (VCC), U14.16 (VCC), U15.14 (VCC), U16.4 (~S), U16.10 (~S), U16.13 (~R), U16.14 (VCC), U17.9 (D), U17.16 (VCC), U18.14 (VCC), X1.14 (Vcc)
